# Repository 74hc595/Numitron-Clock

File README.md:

# IV-19 Numitron Alarm Clock

This is a digital alarm clock that uses Soviet surplus IV-19 (ИВ-19) incandescent ["numitron"](http://www.decadecounter.com/vta/tubepage.php?item=10) displays. 

**[Video overview](https://www.youtube.com/watch?v=N-rBARzu5Fk)**

## Features

The feature set is similar to that of my [Panaplex clock](https://github.com/74hc595/Panaplex-Clock):

- Six digit display (hours/minutes/seconds and month/day/year)
- Powered from a 5V USB charger
- Coin cell battery backup keeps time when unplugged
- Highly accurate oscillator; keeps time within ±3 parts per million
- Piezo beeper alarm
- Automatic leap year correction up to 2099
- Automatic daylight saving time correction (US) up to 2099
- 4-level brightness control
- Sleep mode: can be configured to keep the display blanked and only show the time for a few seconds at the press of a button

## Background

Unlike Nixie tubes, a numitron is not filled with gas and doesn't require high voltage; each segment is literally just an incandescent filament, same as you'd find in a light bulb.

They were a technological stopgap between nixie tubes and LEDs. They also seem to have been used extensively in avionics equipment. (and in the climax of the movie _WarGames_!) I remember seeing them on fuel pumps in the late 1980s.

I found these particular displays on eBay and despite their insane price (US$25 each!) I bought them because of their very uncommon [nine-segment layout](https://en.wikipedia.org/wiki/Nine-segment_display). I've only found evidence of two other people using these displays for projects—and I had to resort to a [Yandex image search](https://yandex.ru/images/search?text=ИВ-20)!

I was able to find a scan of the original Russian datasheet on [Dieter's tube data site](http://www.tube-tester.com/sites/nixie/dat_arch.htm). I've included it in this repo, along with a rough Google translation.

## Hardware

The design is fairly straightforward. Numitrons don't multiplex well, so all 60 segments are direct-driven. They don't require high voltage (I'm driving them with a 3.7V supply) so I used four [STP16CP05](https://www.mouser.com/ProductDetail/STMicroelectronics/STP16CP05MTR/?qs=sGAEpiMZZMvsUbCbgzcXuExUir1Co9YI) constant-current shift register drivers. The segments draw about 22 mA _each_—over an order of magnitude more than LED displays. Multiply that by 60, then multiply that by 3.7, and you'll find that the display draws 4.8 watts with all segments illuminated!

For the brains, I use an [NXP LPC811](https://www.nxp.com/products/processors-and-microcontrollers/arm-based-processors-and-mcus/lpc-cortex-m-mcus/lpc800-series-cortex-m0-plus-mcus/low-cost-microcontrollers-mcus-based-on-arm-cortex-m0-plus-cores:LPC81X_LPC83X)—a relatively bare-bones Arm Cortex-M0+ microcontroller.

Like the Panaplex clock, the enclosure design is an homage to the wood-grain Heathkit clocks from the 1970s, like the [GC-1005](http://tubetime.us/index.php/2012/04/). (Hi Eric!) It's made of 1/8" laser-cut walnut hardwood. The faceplate is transparent 1/8" acrylic, also laser-cut. Unlike neon/Nixie tubes, which emit a very specific wavelength of orange light, the numitron filaments give off a wide spectrum of light, so you can use any color filter you want! I made transparent red, green, and blue faceplates. The blue is best in my opinion—the digits are a deep turquoise color that I haven't been able to photograph successfully.

## Operation

There is a column of three pushbuttons on the back. From top to bottom, they are labeled `+` (Plus), `◉` (Enter), and `−` (Minus).

#### Time display

At the 26th second of even minutes, the date is shown (month/day/year, sorry rest-of-the-world) for 5 seconds. If the backup battery is failing or not present, the display will also briefly show `BAT LO`.

During time display, each button has two functions:

- **Press** `+`: change brightness
- **Hold** `+`: enter sleep mode
- **Press** `◉`: set alarm (see below)
- **Hold** `◉`: set time (see below)
- **Press** `−`: show date for 5 seconds
- **Hold** `−`: enter options menu (see below)

### Setting the time

The hours should be flashing. Use `+`/`−` to change the hour. Press `◉` to advance to the minutes and use `+`/`−` to change the minute. Pressing `◉` finalizes the time, resetting the seconds to :00 and returning you to the normal time display.

Hold `◉` to cancel and return to the normal time display. Any changes to the time are discarded.

### Setting the alarm

The letter `A.` should be flashing. Pressing `+` or `−` toggles the alarm on and off. When the alarm is active, the decimal point of the rightmost digit will illuminate.

Press `◉` to advance to the hours. Use `+`/`−` to change the hour. Press `◉` to advance to the minutes and use `+`/`−` to change the minute.

Hold `◉` to cancel and return to the normal time display. Any changes to the alarm time are discarded.

### Silencing the alarm

When the alarm is going off, hold any button to silence it.

### Alarms and loss of power

The alarm time and state are saved in battery-backed memory. If power is lost, but restored before the alarm's set time, the alarm will go off normally. If power is restored _after_ the alarm's set time, the alarm will _not_ go off.

### Options menu

Pressing `+` and `−` cycle through the menu options:

- `zzz` - turn sleep mode on/off (`Y`/`N`)
- `DATE>` - press `◉` to set date (see below)
- `A.DST` - turn automatic daylight saving time correction on/off (`Y`/`N`)
- `FONT` - switch between 9-segment font (`1`) and 7-segment font (`2`) for time/date display
- `CYCL` - turn date cycling on even minutes on/off (`Y`/`N`)
- `STYLE>` - press `◉` to change time display style (see below)
- Backup battery status: will show `BAT OK` or `BAT LO`
- Firmware version, e.g. `Ver 1.2`
- `DONE>` - press `◉` to return to normal time display

Hold `◉` to cancel and return to the normal time display.

### Setting the date

The month should be flashing. Use `+`/`−` to change the month. Press `◉` to advance to the date and use `+`/`−` to change the date. Press `◉` to advance to the year and use `+`/`−` to change the year. Press `◉` to finalize the date.

Hold `◉` to cancel and return to the menu. Any changes to the date are discarded.

### Setting the display style

Press `+` and `−` to cycle through four time display options:

- `hh.mm.ss` (hour, minute, second)
- `hh.mm` (hour and minute only)
- `h.mm a` (12-hour display with hour, minute, and AM/PM indicator. `◿`=AM, `◸`=PM)
- `hh . mm` (hour and minute only)

Press `◉` to return to the menu.

### Flashing new firmware

Cycle through menu options until the firmware version is displayed. Hold `+` to enter the bootloader. The display will show `---`. You can now connect a 5V FTDI cable and use the `lpc21isp` utility to flash a new firmware image.

To return to normal operation, disconnect and reconnect the power.

## Power considerations

The clock can draw up to 1.5A during operation. It's recommended that you use a high-quality USB power adapter (10 watts or higher), and a "28/24 AWG" USB mini-B cable.

## Version history

### Version 1.2 (March 21, 2019)

- Reduced number of brightness levels to 4.
- Added option to change the number font to one that uses a "standard" 7-segment layout which does not use the diagonal segments. Some may find this more readable.

### Version 1.1 (April 29, 2018)

- 12-hour display style added. Selectable from the `STYLE>` menu. When enabled, 12-hour format with AM/PM indicator (`◿`=AM, `◸`=PM) is used when displaying the time, setting the time, and setting the alarm.

### Version 1.0 (February 11, 2018)

- Initial release

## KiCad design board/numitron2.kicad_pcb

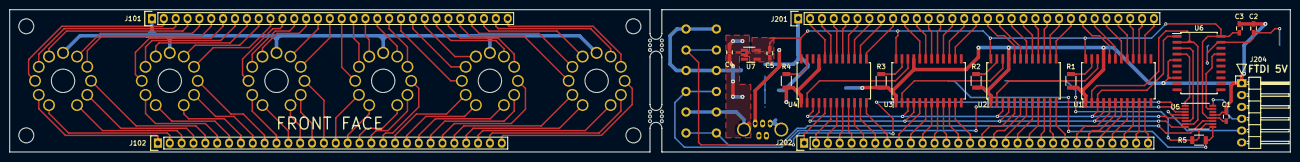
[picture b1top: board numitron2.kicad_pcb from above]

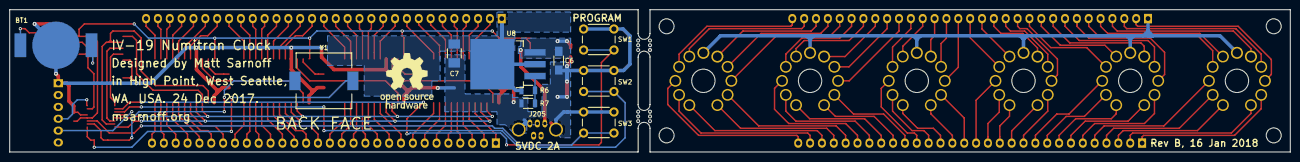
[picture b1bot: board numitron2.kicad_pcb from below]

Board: 2 copper layers, 274.3 x 30.5 mm, 39 parts (11 on the bottom side), 147 nets.

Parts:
BT1: CR2032; BAT-HLD-012-SMT
C1, C2, C3: 0.1uF; C_0603_HandSoldering
C4: 1uF; C_0603_HandSoldering
C5: 2.2uF; C_0603_HandSoldering
C6: 10uF; C_1206_HandSoldering
C7: 10uF; C_1210_HandSoldering
J101: CONN_01X31; Pin_Header_Straight_1x31
J102: CONN_01X30; Pin_Header_Straight_1x30
J201: CONN_01X31; Socket_Strip_Straight_1x31
J202: CONN_01X30; Socket_Strip_Straight_1x30
J204: FTDI (ISP); Pin_Header_Angled_1x06
J205: USB_OTG; UE25BE5510H
N1, N2, N3, N4, N5, N6: IV-19
R1, R2, R3, R4, R6, R7: R; R_1206
R5: 1k; R_1206
SW1, SW2, SW3: SW_Push; SW_PUSH_6mm
U1, U2, U3, U4: STP16CP05; SOIC-24W_7.5x15.4mm_Pitch1.27mm
U5: LPC811M001JDH16; TSSOP-16_4.4x5mm_Pitch0.65mm
U6: PCF2129AT; SOIC-20W_7.5x12.8mm_Pitch1.27mm
U7: TPS70933; SOT-23-5_HandSoldering
U8: LM1085ISX-ADJ/NOPB; TO-263-3Lead
Y1: PKLCS1212E2000-R1; PKLCS1212

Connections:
+3V3: C1.1, C3.1, C5.1, U1.24, U2.24, U3.24, U4.24, U5.12, U6.20, U7.5
+5V: C4.1, C6.1, J205.1, U7.1, U8.3
/1A: J101.4, N1.7
/1A': J201.4, U4.18
/1B: J101.5, N1.5
/1B': J201.5, U4.17
/1C: J102.3, N1.1
/1C': J202.3, U4.7
/1D: J102.1, N1.10
/1D': J202.1, U4.5
/1DP: J102.4, N1.2
/1DP': J202.4, U4.8
/1E: J101.2, N1.9
/1E': J201.2, U4.20
/1F: J101.3, N1.8
/1F': J201.3, U4.19
/1G: J102.5, N1.3
/1G': J202.5, U4.9
/1H: J101.6, N1.4
/1H': J201.6, U4.16
/1I: J102.2, N1.11
/1I': J202.2, U4.6
/2A: J101.9, N2.7
/2A': J201.9, U4.13
/2B: J101.10, N2.5
/2B': J201.10, U3.20
/2C: J102.8, N2.1
/2C': J202.8, U4.12
/2D: J102.6, N2.10
/2D': J202.6, U4.10
/2DP: J102.9, N2.2
/2DP': J202.9, U3.5
/2E: J101.7, N2.9
/2E': J201.7, U4.15
/2F: J101.8, N2.8
/2F': J201.8, U4.14
/2G: J102.10, N2.3
/2G': J202.10, U3.6
/2H: J101.11, N2.4
/2H': J201.11, U3.19
/2I: J102.7, N2.11
/2I': J202.7, U4.11
/3A: J101.14, N3.7
/3A': J201.14, U3.16
/3B: J101.15, N3.5
/3B': J201.15, U3.15
/3C: J102.13, N3.1
/3C': J202.13, U3.9
/3D: J102.11, N3.10
/3D': J202.11, U3.7
/3DP: J102.14, N3.2
/3DP': J202.14, U3.10
/3E: J101.12, N3.9
/3E': J201.12, U3.18
/3F: J101.13, N3.8
/3F': J201.13, U3.17
/3G: J102.15, N3.3
/3G': J202.15, U3.11
/3H: J101.16, N3.4
/3H': J201.16, U3.14
/3I: J102.12, N3.11
/3I': J202.12, U3.8
/4A: J101.19, N4.7
/4A': J201.19, U2.18
/4B: J101.20, N4.5
/4B': J201.20, U2.17
/4C: J102.18, N4.1
/4C': J202.18, U2.7
/4D: J102.16, N4.10
/4D': J202.16, U2.5
/4DP: J102.19, N4.2
/4DP': J202.19, U2.8
/4E: J101.17, N4.9
/4E': J201.17, U2.20
/4F: J101.18, N4.8
/4F': J201.18, U2.19
/4G: J102.20, N4.3
/4G': J202.20, U2.9
/4H: J101.21, N4.4
/4H': J201.21, U2.16
/4I: J102.17, N4.11
/4I': J202.17, U2.6
/5A: J101.24, N5.7
/5A': J201.24, U2.13
/5B: J101.25, N5.5
/5B': J201.25, U1.20
/5C: J102.23, N5.1
/5C': J202.23, U2.12
/5D: J102.21, N5.10
/5D': J202.21, U2.10
/5DP: J102.24, N5.2
/5DP': J202.24, U1.5
/5E: J101.22, N5.9
/5E': J201.22, U2.15
/5F: J101.23, N5.8
/5F': J201.23, U2.14
/5G: J102.25, N5.3
/5G': J202.25, U1.6
/5H: J101.26, N5.4
/5H': J201.26, U1.19
/5I: J102.22, N5.11
/5I': J202.22, U2.11
/6A: J101.29, N6.7
/6A': J201.29, U1.16
/6B: J101.30, N6.5
/6B': J201.30, U1.15
/6C: J102.28, N6.1
/6C': J202.28, U1.9
/6D: J102.26, N6.10
/6D': J202.26, U1.7
/6DP: J102.29, N6.2
/6DP': J202.29, U1.10
/6E: J101.27, N6.9
/6E': J201.27, U1.18
/6F: J101.28, N6.8
/6F': J201.28, U1.17
/6G: J102.30, N6.3
/6G': J202.30, U1.11
/6H: J101.31, N6.4
/6H': J201.31, U1.14
/6I: J102.27, N6.11
/6I': J202.27, U1.8
/LATCH: U1.4, U2.4, U3.4, U4.4, U5.8
/MISO: U5.6, U6.3
/MOSI: U1.2, U5.7, U6.2
/RX: J204.4, U5.16
/SCK: U1.3, U2.3, U3.3, U4.3, U5.5, U6.1
/SPKR1: R5.1, U5.10, Y1.1
/SPKR2: R5.2, U5.9, Y1.2
/SW1: SW1.1, U5.2
/SW2: SW2.1, U5.3
/SW3: SW3.1, U5.11
/TX: J204.5, U5.4
/VNN: J101.1, N1.6, N2.6, N3.6, N4.6, N5.6, N6.6
/VNN': C7.1, J201.1, R6.1, U8.2
/~RTC_INT: U5.15, U6.17
/~RTC_SS: U5.1, U6.4
GND: BT1.2, C1.2, C2.2, C3.2, C4.2, C5.2, C6.2, C7.2, J204.1, J205.5, J205.6, R1.2, R2.2, R3.2, R4.2, R7.2, SW1.2, SW2.2, SW3.2, U1.1, U1.21, U2.1, U2.21, U3.1, U3.21, U4.1, U4.21, U5.13, U6.5, U6.8, U7.2, U7.4
unnamed: BT1.1, C2.1, U6.19
unnamed: R1.1, U1.23
unnamed: R2.1, U2.23
unnamed: R3.1, U3.23
unnamed: R4.1, U4.23
unnamed: R6.2, R7.1, U8.1
unnamed: U1.22, U2.2
unnamed: U2.22, U3.2
unnamed: U3.22, U4.2

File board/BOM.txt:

IV-19 Numitron Clock Bill of Materials
======================================

BT1                     12mm coin cell holder, SMD, Linx BAT-HLD-012-SMT
C1, C2, C3              0.1uF multilayer ceramic capacitor, 16V or higher, 0603
C4                      1uF X7R multilayer ceramic capacitor, 16V or higher, 0603
C5                      2.2uF X7R multilayer ceramic capacitor, 16V or higher, 0603
C6                      10uF multilayer ceramic capacitor, 25V, 1206, AVX 12063C106KAT2A
C7                      10uF tantalum capacitor, 20V, 1210, AVX TAJB106K020RNJV
J101                    1x31 0.1" straight header pin
J102                    1x30 0.1" straight header pin
J201                    1x31 0.1" straight header socket
J202                    1x30 0.1" straight header socket
J204                    1x6 0.1" right-angle header pin
J205                    USB-B mini socket, straight, Amphenol UE25BE5510H
N1, N2, N3, N4, N5, N6  IV-19 numitron tube (eBay)
                        Pin sockets: Mill-Max 0327-0-15-15-34-27-10-0, qty 60
R1, R2, R3, R4, R5      910 ohm resistor, 1/8 watt, 1206
R6                      240 ohm resistor, 1/8 watt, 1206
R7                      470 ohm resistor, 1/8 watt, 1206
SW1, SW2, SW3           Tactile switch, 6mm, through hole, 13mm actuator
U1, U2, U3, U4          Display driver, ST STP16CP05MTR
U5                      Cortex-M0+ microcontroller, NXP LPC811M001JDH16J
U6                      Real-time clock, NXP PCF2129AT/2,518
U7                      3.3V LDO regulator, TI TPS70933DBVR
U8                      3A adjustable LDO regulator, TI LM1085ISX-ADJ/NOPB
Y1                      Piezo sounder, Murata PKLCS1212E2000-R1

(J203 omitted)

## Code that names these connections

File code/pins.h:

#ifndef PINS_H_
#define PINS_H_
#ifdef __cplusplus
extern "C" {
#endif

#include "LPC8xx.h"

/* Pin configuration:
  1	   SPI0_SSEL  (/RTC_SS) Slave Select for SPI0.
  2    PIO0_12    (SW1) General purpose digital input/output pin.
  3    PIO0_5     (SW2) General purpose digital input/output pin.
  4    U0_TXD     Transmitter output for USART0.
  5    SPI0_SCK   Serial clock for SPI0.
  6    SPI0_MISO  Master In Slave Out for SPI0.
  7    PIO0_11    (unused) General purpose digital input/output pin.
  8    PIO0_10    (LATCH) General purpose digital input/output pin.
  9    CTOUT_1    (SPKR2) SCT output 1.
  10   CTOUT_0    (SPKR1) SCT output 0.
  11   PIO0_8     (SW3) General purpose digital input/output pin.
  12   VDD        VDD
  13   VSS        VSS
  14   SPI0_MOSI  Master Out Slave In for SPI0.
  15   PIO0_6     (/RTC_INT) General purpose digital input/output pin.
  16   U0_RXD     Receiver input for USART0.
*/
#define PIN_nRTC_SS   13
#define PIN_SW1       12
#define PIN_SW2       5
#define PIN_SCK       3
#define PIN_MISO      2
#define PIN_LATCH     10
#define PIN_SPKR2     1
#define PIN_SPKR1     9
#define PIN_MOSI      7
#define PIN_SW3       8
#define PIN_nRTC_INT  6

/* this is an AVR-GCC idiom */
#define _BV(n)            (1UL<<(n))

#define pins_input(bits)  LPC_GPIO_PORT->DIR0 &= ~(bits)
#define pins_output(bits) LPC_GPIO_PORT->DIR0 |=  (bits)
#define pins_high(bits)   LPC_GPIO_PORT->SET0 =   (bits)
#define pins_low(bits)    LPC_GPIO_PORT->CLR0 =   (bits)

#define pin_input(p)      pins_input(_BV(p))
#define pin_output(p)     pins_output(_BV(p))
#define pin_high(p)       pins_high(_BV(p))
#define pin_low(p)        pins_low(_BV(p))

void pins_init(void);

#ifdef __cplusplus
}
#endif
#endif

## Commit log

2018-02-12 initial import
2018-02-12 add bill of materials
2018-02-12 code readme; remove outdated comment
2018-02-12 add IV-19 tube data
2018-02-12 add readme
2018-02-12 Create LICENSE
2018-02-12 Add video link
2018-02-13 add parenthesis
2018-02-13 consistent indents in makefile
2018-04-29 add 12-hour display style
    replaces the weird fake colon style
    Version 1.1
2020-01-25 Version 1.2
    - reduce brightness levels to 4
    - add option to switch between 9-segment and 7-segment font
